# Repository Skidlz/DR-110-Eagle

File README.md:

# DR-110-Eagle
DR-110 Schematics and Board Layout

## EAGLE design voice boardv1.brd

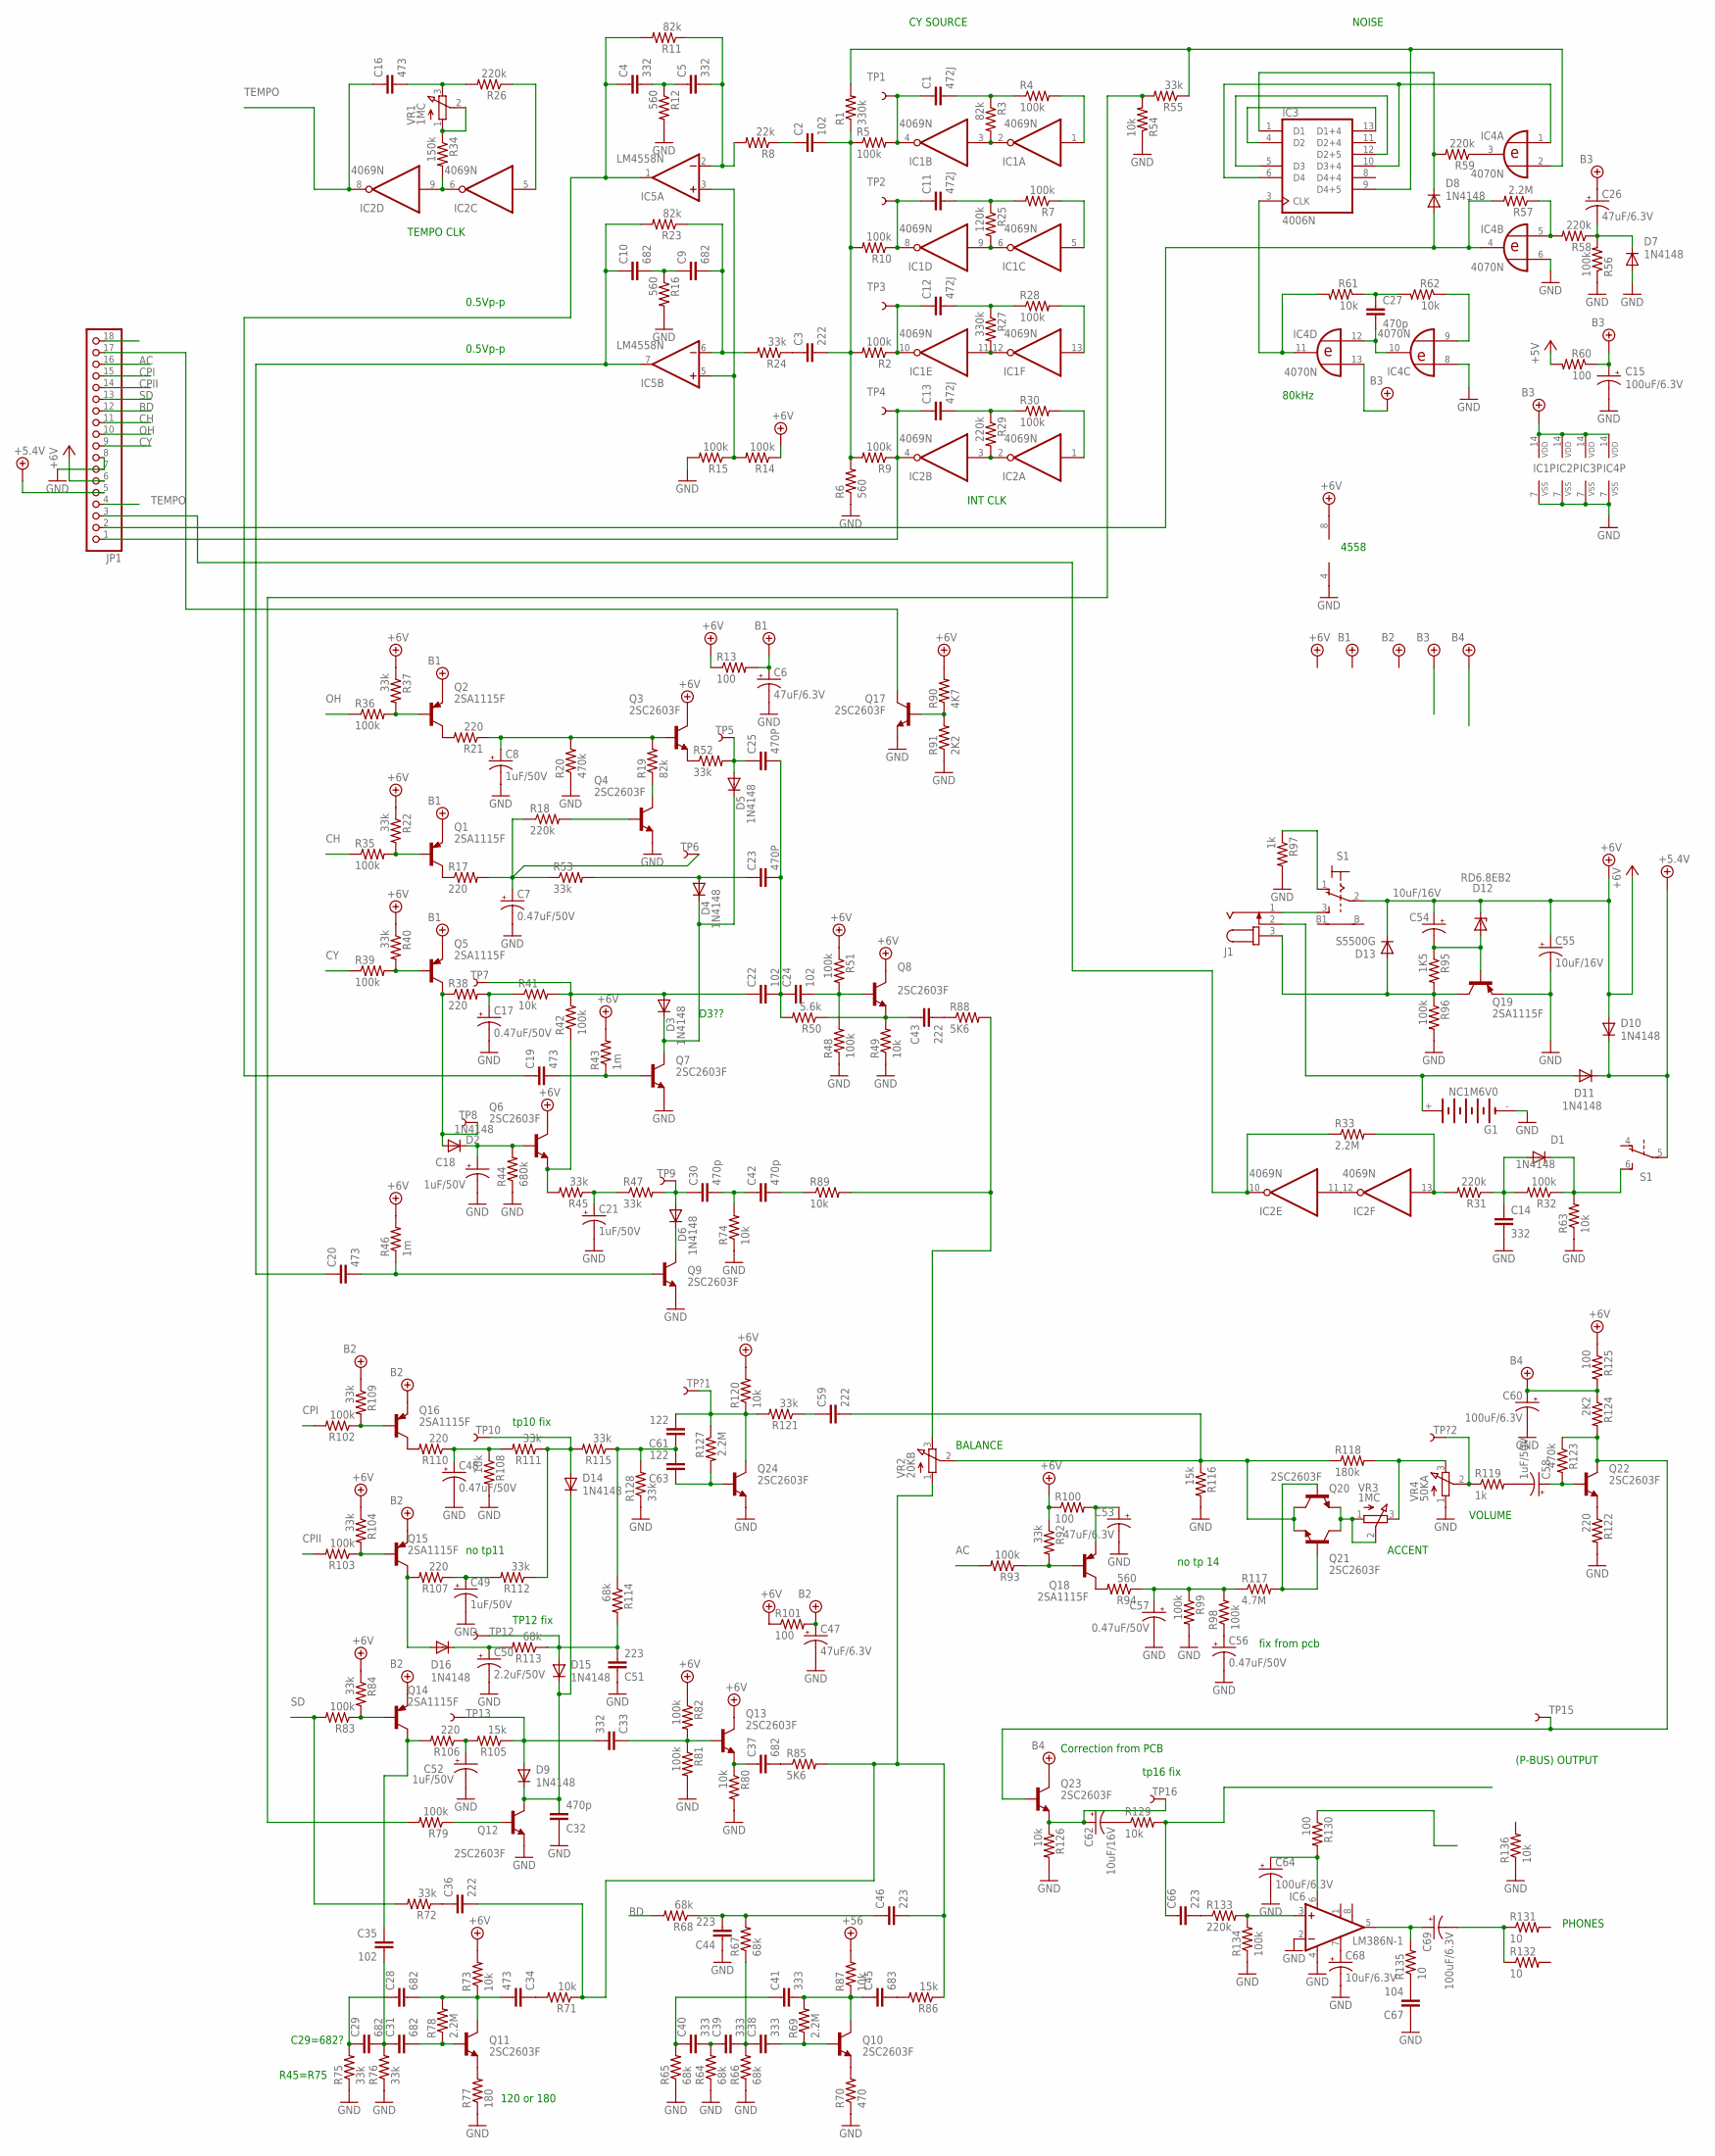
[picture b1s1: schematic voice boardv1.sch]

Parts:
C1, C11, C12, C13: 472J; C050-024X044
C2, C22, C24, C35: 102; C050-024X044
C3, C36, C43, C59: 222; C050-024X044
C4, C5, C14, C33: 332; C050-024X044
C6, C26, C47, C53: 47uF/6.3V; B45181B
C7, C17, C48, C56, C57: 0.47uF/50V; B45181B
C8, C18, C21, C49, C52, C58: 1uF/50V; B45181B
C9, C10, C28, C29, C31, C37: 682; C050-024X044
C15, C60, C64, C69: 100uF/6.3V; B45181B
C16, C19, C20, C34: 473; C050-024X044
C23, C25: 470P; C050-024X044
C27, C30, C32, C42: 470p; C050-024X044
C38, C39, C40, C41: 333; C050-024X044
C44, C46, C51, C66: 223; C050-024X044
C45: 683; C050-024X044
C50: 2.2uF/50V; B45181B
C54, C55, C62: 10uF/16V; B45181B
C61, C63: 122; C050-024X044
C67: 104; C050-024X044
C68: 10uF/6.3V; B45181B
D1, D2, D3, D4, D5, D6, D7, D8, D9, D10, D11, D14, D15, D16: 1N4148; D-5
D12: RD6.8EB2; ZDIO-5
D13: S5500G; D-5
G1: NC1M6V0; NC1M
IC1, IC2: 4069N; DIL14
IC3: 4006N; DIL14
IC4: 4070N; DIL14
IC5: LM4558N; DIL08
IC6: LM386N-1; DIL08
J1: JACK-PLUG0; SPC4077
JP1: PINHD-1X18; 1X18
Q1, Q2, Q5, Q14, Q15, Q16, Q18, Q19: 2SA1115F; TO92-ECB
Q3, Q4, Q6, Q7, Q8, Q9, Q10, Q11, Q12, Q13, Q17, Q20, Q21, Q22, Q23, Q24: 2SC2603F; TO92-ECB
R1, R27: 330k; 0204/5
R2, R4, R5, R7, R9, R10, R14, R15, R28, R30, R32, R35, R36, R39, R42, R48, R51, R56, R79, R81, R82, R83, R93, R96, R98, R99, R102, R103, R134: 100k; 0204/5
R3, R11, R19, R23: 82k; 0204/5
R6, R12, R16, R94: 560; 0204/5
R8: 22k; 0204/5
R13, R60, R100, R101, R125, R130: 100; 0204/5
R17, R21, R38, R106, R107, R110, R122: 220; 0204/5
R18, R26, R29, R31, R58, R59, R133: 220k; 0204/5
R20, R123: 470k; 0204/5
R22, R24, R37, R40, R45, R47, R52, R53, R55, R72, R75, R76, R84, R92, R104, R109, R111, R112, R115, R121, R128: 33k; 0204/5
R25: 120k; 0204/5
R33, R57, R69, R78, R127: 2.2M; 0204/5
R34: 150k; 0204/5
R41, R49, R54, R61, R62, R63, R71, R73, R74, R80, R87, R89, R108, R120, R126, R129, R136: 10k; 0204/5
R43, R46: 1m; 0204/5
R44: 680k; 0204/5
R50: 5.6k; 0204/5
R64, R65, R66, R67, R68, R113, R114: 68k; 0204/5
R70: 470; 0204/5
R77: 180; 0204/5
R85, R88: 5K6; 0204/5
R86, R105, R116: 15k; 0204/5
R90: 4K7; 0204/5
R91, R124: 2K2; 0204/5
R95: 1K5; 0204/5
R97, R119: 1k; 0204/5
R117: 4.7M; 0204/5
R118: 180k; 0204/5
R131, R132, R135: 10; 0204/5
S1: 9070-2W
TP1, TP2, TP3, TP4, TP5, TP6, TP7, TP8, TP9, TP10, TP12, TP13, TP15, TP16: TEST-POINT3X5; PAD.03X.05
TP?1, TP?2: TEST-POINT3X5; PAD.03X.05
VR1, VR3: 1MC; EVUF
VR2: 20KB; EVUF
VR4: 50KA; EVUF

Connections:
+4.1V: D10.C, D11.C, JP1.5, S1.5
+5V: C54.+, C55.+, D10.A, D12.C, D13.C, IC5.8 (V+), JP1.6, Q3.C, Q6.C, Q8.C, Q13.C, R13.1, R14.1, R22.1, R37.1, R40.1, R43.2, R46.2, R51.1, R60.2, R73.2, R82.1, R84.1, R87.2, R90.2, R92.1, R100.1, R101.1, R104.1, R120.2, R125.1, S1.2
+5V/1: C6.+, Q1.E, Q2.E, Q5.E, R13.2
+5V/2: C47.+, Q14.E, Q15.E, Q16.E, R101.2, R109.1
+5V/3: C15.+, C26.+, IC1.14 (VDD), IC2.14 (VDD), IC3.14 (VDD), IC4.13 (I1), IC4.14 (VDD), R60.1
+5V/4: C60.+, Q23.C, R124.1, R125.2
AC: JP1.16, R93.2
BD: JP1.12, R68.2
CH: JP1.11, R35.1
CPI: JP1.15, R102.2
CPII: JP1.14, R103.2
CY: JP1.9, R39.1
GND: C6.-, C7.-, C8.-, C14.2, C15.-, C17.-, C18.-, C21.-, C32.1, C44.1, C47.-, C48.-, C49.-, C50.-, C51.1, C52.-, C53.-, C55.-, C56.-, C57.-, C60.-, C64.-, C67.1, C68.-, D7.A, G1.-, IC1.7 (VSS), IC2.7 (VSS), IC3.7 (VSS), IC4.6 (I1), IC4.7 (VSS), IC4.8 (I0), IC5.4 (V-), IC6.2 (-IN), IC6.4 (GND), JP1.7, JP1.8, Q4.E, Q7.E, Q9.E, Q12.E, Q17.E, Q19.E, Q24.E, R6.1, R12.2, R15.2, R16.2, R20.1, R44.1, R48.1, R49.1, R54.1, R56.1, R63.1, R64.1, R65.1, R66.1, R70.1, R74.1, R75.1, R76.1, R77.1, R80.2, R81.2, R91.1, R96.2, R97.2, R99.2, R108.2, R116.2, R122.2, R126.2, R128.1, R134.1, R136.1, VR4.1 (A)
unnamed: IC1.2 (O), IC1.3 (I), R3.2
unnamed: IC1.6 (O), IC1.9 (I), R25.2
unnamed: IC1.11 (I), IC1.12 (O), R27.2
unnamed: IC2.2 (O), IC2.3 (I), R29.2
unnamed: IC2.6 (O), IC2.9 (I), R34.2
unnamed: IC2.11 (I), IC2.12 (O)
unnamed: C12.1, IC1.10 (O), R2.1, TP3.P$1
unnamed: C1.2, R3.1, R4.1
unnamed: C1.1, IC1.4 (O), R5.2, TP1.P$1
unnamed: C13.1, IC2.4 (O), JP1.1, R9.1, TP4.P$1
unnamed: C11.1, IC1.8 (O), R10.1, TP2.P$1
unnamed: C2.2, C3.2, R1.1, R2.2, R5.1, R6.2, R9.2, R10.2
unnamed: IC1.1 (I), R4.2
unnamed: IC1.5 (I), R7.1
unnamed: IC1.13 (I), R28.2
unnamed: C5.2, IC5.2 (-IN), R8.2, R11.1
unnamed: C4.1, C19.1, IC5.1 (OUT), R11.2
unnamed: C4.2, C5.1, R12.1
unnamed: IC5.3 (+IN), IC5.5 (+IN), R14.2, R15.1
unnamed: C2.1, R8.1
unnamed: C7.+, R17.2, R18.1, R53.1, TP6.P$1
unnamed: C8.+, Q3.B, R19.2, R20.2, R21.1
unnamed: Q4.B, R18.2
unnamed: Q4.C, R19.1
unnamed: Q2.C, R21.2
unnamed: Q1.C, R17.1
unnamed: Q1.B, R22.2, R35.2
unnamed: C9.1, C10.2, R16.1
unnamed: C3.1, R24.1
unnamed: C10.1, C20.1, IC5.7 (OUT), R23.2
unnamed: C9.2, IC5.6 (-IN), R23.1, R24.2
unnamed: C12.2, R27.1, R28.1
unnamed: C11.2, R7.2, R25.1
unnamed: C13.2, R29.1, R30.1
unnamed: IC2.1 (I), R30.2
unnamed: C14.1, D1.A, R31.1, R32.2
unnamed: IC2.5 (I), R26.1
unnamed: C16.2, R26.2, VR1.3 (E)
unnamed: IC3.9 (D4+5), IC4.2 (I1), R1.2, R55.1
unnamed: IC3.4 (D2), IC3.13 (D1+4)
unnamed: IC3.6 (D4), IC3.10 (D3+4), IC4.1 (I0)
unnamed: IC3.5 (D3), IC3.12 (D2+5)
unnamed: D8.C, IC3.1 (D1), R59.2
unnamed: D1.C, R32.1, R63.2, S1.6 (S)
unnamed: IC3.3 (CLK), IC4.11 (O), R61.2
unnamed: C18.+, D2.C, Q6.B, R44.2
unnamed: D2.A, Q5.C, R38.1, TP8.P$1
unnamed: C19.2, Q7.B, R43.1
unnamed: C20.2, Q9.B, R46.1
unnamed: C22.2, C23.2, C24.1, C25.2, R50.2
unnamed: IC2.13 (I), R31.2, R33.2
unnamed: IC2.10 (O), JP1.3, R33.1
unnamed: R34.1, VR1.1 (A), VR1.2 (S)
unnamed: Q2.B, R36.2, R37.2
unnamed: Q5.B, R39.2, R40.2
unnamed: C17.+, R38.2, R41.1
unnamed: C22.1, D3.A, R41.2, R42.2, TP7.P$1
unnamed: Q6.E, R42.1, R45.2
unnamed: C21.+, R45.1, R47.1
unnamed: C24.2, Q8.B, R48.2, R51.2
unnamed: D3.C, D4.C, D5.C, Q7.C
unnamed: C23.1, D4.A, R53.2
unnamed: C25.1, D5.A, R52.2, TP5.P$1
unnamed: C43.1, Q8.E, R49.2, R50.1
unnamed: Q3.E, R52.1
unnamed: C30.1, D6.A, R47.2, TP9.P$1
unnamed: D6.C, Q9.C
unnamed: R54.2, R55.2, R79.2
unnamed: IC4.5 (I0), R57.1, R58.2
unnamed: C26.-, D7.C, R56.2, R58.1
unnamed: D8.A, IC4.4 (O), JP1.2, R57.2
unnamed: C38.2, Q10.B, R69.1
unnamed: IC4.3 (O), R59.1
unnamed: C27.1, R61.1, R62.2
unnamed: IC4.9 (I1), R62.1
unnamed: C27.2, IC4.10 (O), IC4.12 (I0)
unnamed: Q10.E, R70.2
unnamed: C41.2, C45.1, Q10.C, R69.2, R87.1
unnamed: C38.1, C39.2, R66.2, R67.1
unnamed: C44.2, C46.1, R67.2, R68.1
unnamed: C31.2, Q11.B, R78.1
unnamed: C29.2, C31.1, C35.2, R76.2
unnamed: C28.1, C29.1, R75.2
unnamed: C40.1, C41.1, R65.2
unnamed: C32.2, D9.C, D14.C, D15.C, Q12.C
unnamed: C42.2, R89.1
unnamed: C37.1, Q13.E, R80.1
unnamed: C39.1, C40.2, R64.2
unnamed: C34.1, R71.2
unnamed: Q12.B, R79.1
unnamed: C36.1, R72.1
unnamed: C56.+, R98.1
unnamed: C30.2, C42.1, R74.2
unnamed: Q11.E, R77.2
unnamed: C28.2, C34.2, Q11.C, R73.1, R78.2
unnamed: C36.2, C46.2, R71.1, R85.2, R86.1, VR2.1 (A)
unnamed: JP1.17, Q17.C
unnamed: C33.1, Q13.B, R81.1, R82.2
unnamed: R88.2, R89.2, VR2.3 (E)
unnamed: Q14.B, R83.1, R84.2
unnamed: C35.1, Q14.C, R106.2
unnamed: C33.2, D9.A, R105.1, TP13.P$1
unnamed: C37.2, R85.1
unnamed: C45.2, R86.2
unnamed: C43.2, R88.1
unnamed: Q17.B, R90.1, R91.2
unnamed: Q18.B, R92.2, R93.1
unnamed: Q18.C, R94.2
unnamed: C53.+, Q18.E, R100.2
unnamed: R118.2, VR3.3 (E), VR4.3 (E)
unnamed: D13.A, J1.3, Q19.C, R95.2, R96.1
unnamed: D11.A, G1.+, J1.2
unnamed: C54.-, D12.A, Q19.B, R95.1
unnamed: R97.1, S1.1 (O)
unnamed: J1.1, S1.3 (S)
unnamed: C57.+, R94.1, R98.2, R99.1, R117.1
unnamed: Q15.B, R103.1, R104.2
unnamed: Q16.B, R102.1, R109.2
unnamed: C52.+, R105.2, R106.1
unnamed: D16.A, Q15.C, R107.2
unnamed: Q16.C, R110.2
unnamed: C48.+, R108.1, R110.1, R111.2
unnamed: C49.+, R107.1, R112.2
unnamed: D14.A, R111.1, R112.1, R115.2, TP10.P$1
unnamed: C61.1, C63.2, R114.1, R115.1, R128.2
unnamed: C50.+, D16.C, R113.2
unnamed: C51.2, D15.A, R113.1, R114.2, TP12.P$1
unnamed: Q20.B, Q21.B, R117.2
unnamed: C59.2, Q20.C, Q21.E, R116.1, R118.1, VR2.2 (S)
unnamed: Q20.E, Q21.C, VR3.1 (A), VR3.2 (S)
unnamed: R119.1, TP?2.P$1, VR4.2 (S)
unnamed: C61.2, Q24.C, R120.1, R121.2, R127.1, TP?1.P$1
unnamed: Q22.E, R122.1
unnamed: Q22.C, Q23.B, R123.1, R124.2, TP15.P$1
unnamed: C58.+, Q22.B, R123.2
unnamed: C62.+, Q23.E, R126.1, TP16.P$1
unnamed: C68.+, IC6.7 (BYPASS)
unnamed: C63.1, Q24.B, R127.2
unnamed: C58.-, R119.2
unnamed: C59.1, R121.1
unnamed: C62.-, R129.1
unnamed: C66.1, R129.2
unnamed: C64.+, IC6.6 (VS), R130.2
unnamed: C69.+, IC6.5 (OUT), R135.2
unnamed: C69.-, R131.1, R132.1
unnamed: IC6.3 (+IN), R133.2, R134.2
unnamed: C66.2, R133.1
unnamed: C67.2, R135.1
OH: JP1.10, R36.1
SD: JP1.13, R72.2, R83.2
TEMPO: C16.1, IC2.8 (O), JP1.4

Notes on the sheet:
D3??
80kHz
C29=682?
R45=R75
120 or 180
4558
Correction from PCB
TP12 fix
tp10 fix
tp16 fix
no tp11
no tp 14
fix from pcb
TEMPO CLK
INT CLK
CY SOURCE
NOISE
BALANCE
VOLUME
ACCENT
PHONES
(P-BUS) OUTPUT
0.5Vp-p

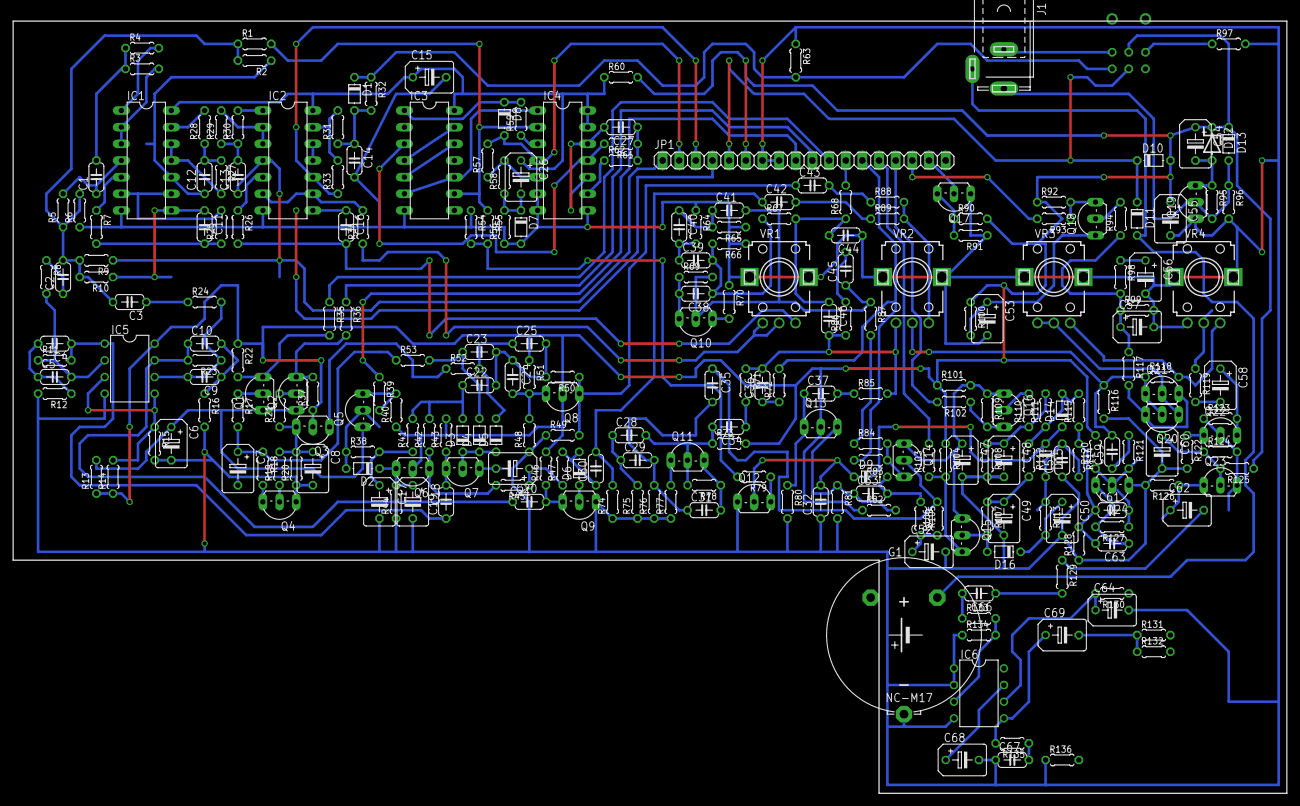
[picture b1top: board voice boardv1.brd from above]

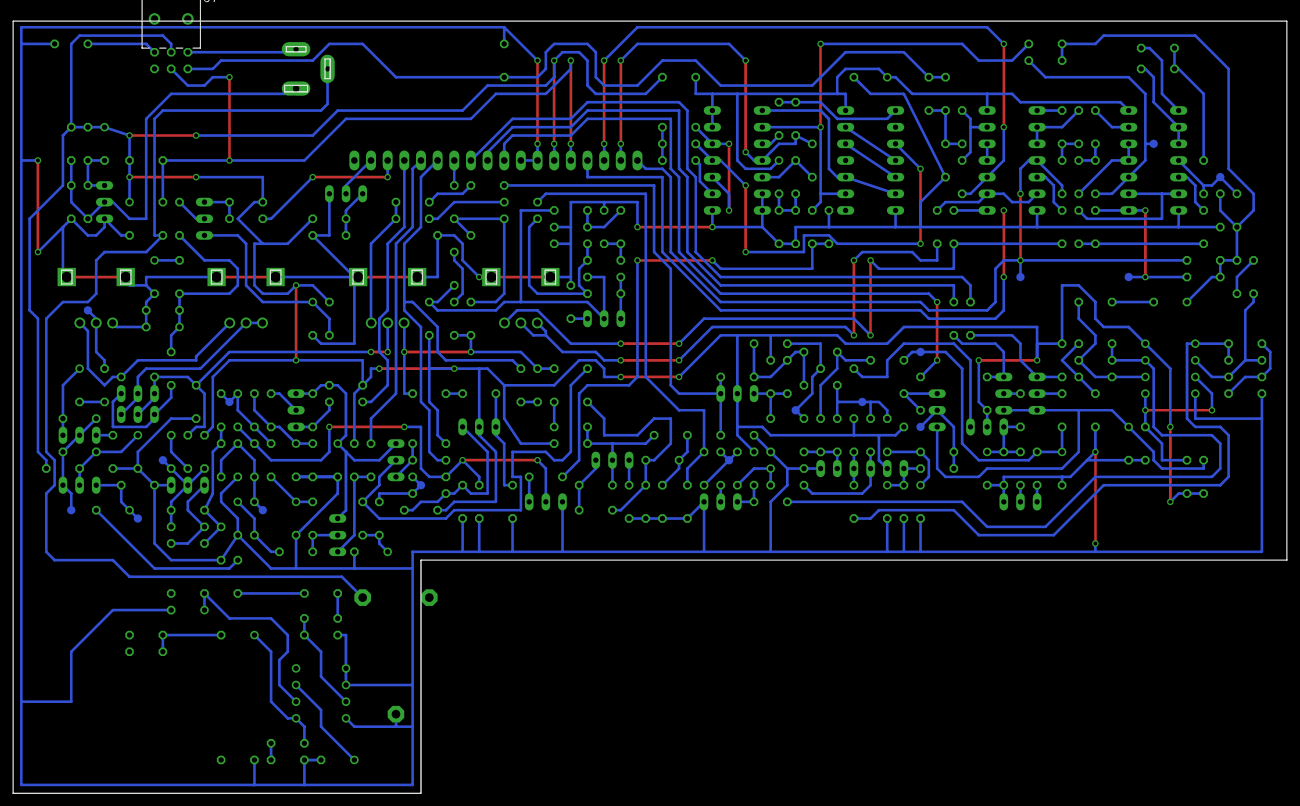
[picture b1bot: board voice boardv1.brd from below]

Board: 2 copper layers, 194.3 x 117.8 mm, 274 parts (17 on the bottom side), 164 nets.

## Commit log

2015-11-27 Images

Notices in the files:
parts and their libraries:
SparkFun-Passives: Licensing: CC v3.0 Share-Alike You are welcome to use this library for commercial purposes.
